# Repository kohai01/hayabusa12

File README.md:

# hayabusa12
hayabusa12 is a brother of hayabusa04 with more keys and an oled display
It allows the users to bind any macros to every key.
Now with the equipped oled display, you can customize your macropad with your favorite artwork!

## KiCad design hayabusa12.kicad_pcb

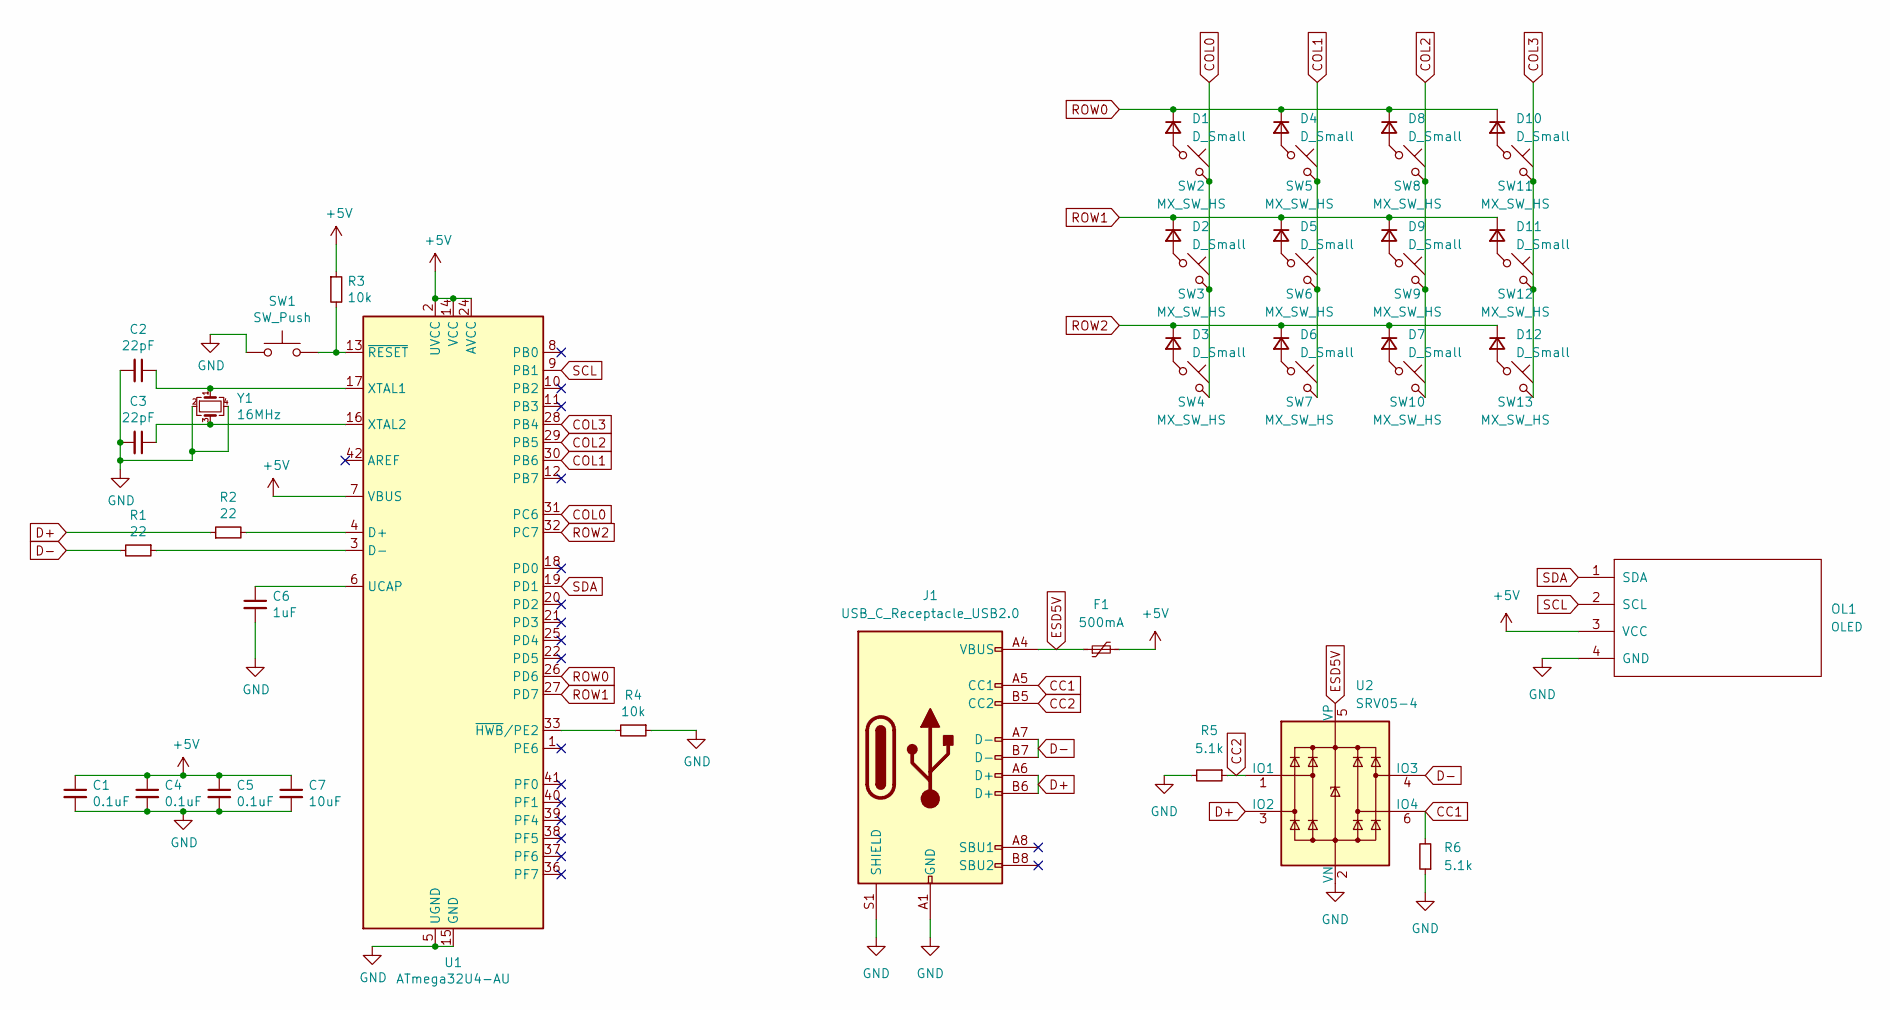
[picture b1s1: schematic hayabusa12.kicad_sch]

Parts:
C1, C4, C5: 0.1uF; C_0805_2012Metric
C2, C3: 22pF; C_0805_2012Metric
C6: 1uF; C_0805_2012Metric
C7: 10uF; C_0805_2012Metric
D1, D2, D3, D4, D5, D6, D7, D8, D9, D10, D11, D12: D_Small; D_SOD-123
F1: 500mA; Fuse_1206_3216Metric
J1: USB_C_Receptacle_USB2.0; USB_C_Receptacle_HRO_TYPE-C-31-M-12
OL1: OLED; OLED_v2
R1, R2: 22; R_0805_2012Metric
R3, R4: 10k; R_0805_2012Metric
R5, R6: 5.1k; R_0805_2012Metric
SW1: SW_Push; SW_SPST_SKQG_WithStem
SW2, SW3, SW4, SW5, SW6, SW7, SW8, SW9, SW10, SW11, SW12, SW13: MX_SW_HS; SW_MX_HS_1u
U1: ATmega32U4-AU; TQFP-44_10x10mm_P0.8mm
U2: SRV05-4; SOT-23-6
Y1: 16MHz; Crystal_SMD_3225-4Pin_3.2x2.5mm

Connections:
+5V: C1.1, C4.1, C5.1, C7.1, F1.2, OL1.3 (VCC), R3.1, U1.2 (UVCC), U1.7 (VBUS), U1.14 (VCC), U1.24 (AVCC), U1.34 (VCC), U1.44 (AVCC)
CC1: J1.A5 (CC1), R6.2, U2.6 (IO4)
CC2: J1.B5 (CC2), R5.1, U2.1 (IO1)
COL0: SW2.2, SW3.2, SW4.2, U1.31 (PC6)
COL1: SW5.2, SW6.2, SW7.2, U1.30 (PB6)
COL2: SW8.2, SW9.2, SW10.2, U1.29 (PB5)
COL3: SW11.2, SW12.2, SW13.2, U1.28 (PB4)
D+: J1.A6 (D+), J1.B6 (D+), R2.1, U2.3 (IO2)
D-: J1.A7 (D-), J1.B7 (D-), R1.2, U2.4 (IO3)
ESD5V: F1.1, J1.A4 (VBUS), J1.A9 (VBUS), J1.B4 (VBUS), J1.B9 (VBUS), U2.5 (VP)
GND: C1.2, C2.2, C3.2, C4.2, C5.2, C6.2, C7.2, J1.A1 (GND), J1.A12 (GND), J1.B1 (GND), J1.B12 (GND), J1.S1 (SHIELD), OL1.4 (GND), R4.1, R5.2, R6.1, SW1.1, U1.5 (UGND), U1.15 (GND), U1.23 (GND), U1.35 (GND), U1.43 (GND), U2.2 (VN), Y1.2, Y1.4
unnamed: C2.1, U1.17 (XTAL1), Y1.1
unnamed: C3.1, U1.16 (XTAL2), Y1.3
unnamed: C6.1, U1.6 (UCAP)
unnamed: D1.2 (A), SW2.1
unnamed: D2.2 (A), SW3.1
unnamed: D3.2 (A), SW4.1
unnamed: D4.2 (A), SW5.1
unnamed: D5.2 (A), SW6.1
unnamed: D6.2 (A), SW7.1
unnamed: D7.2 (A), SW10.1
unnamed: D8.2 (A), SW8.1
unnamed: D9.2 (A), SW9.1
unnamed: D10.2 (A), SW11.1
unnamed: D11.2 (A), SW12.1
unnamed: D12.2 (A), SW13.1
unnamed: R1.1, U1.3 (D-)
unnamed: R2.2, U1.4 (D+)
unnamed: R3.2, SW1.2, U1.13 (~RESET)
unnamed: R4.2, U1.33 (~HWB/PE2)
ROW0: D1.1 (K), D4.1 (K), D8.1 (K), D10.1 (K), U1.26 (PD6)
ROW1: D2.1 (K), D5.1 (K), D9.1 (K), D11.1 (K), U1.27 (PD7)
ROW2: D3.1 (K), D6.1 (K), D7.1 (K), D12.1 (K), U1.32 (PC7)
SCL: OL1.2 (SCL), U1.9 (PB1)
SDA: OL1.1 (SDA), U1.19 (PD1)

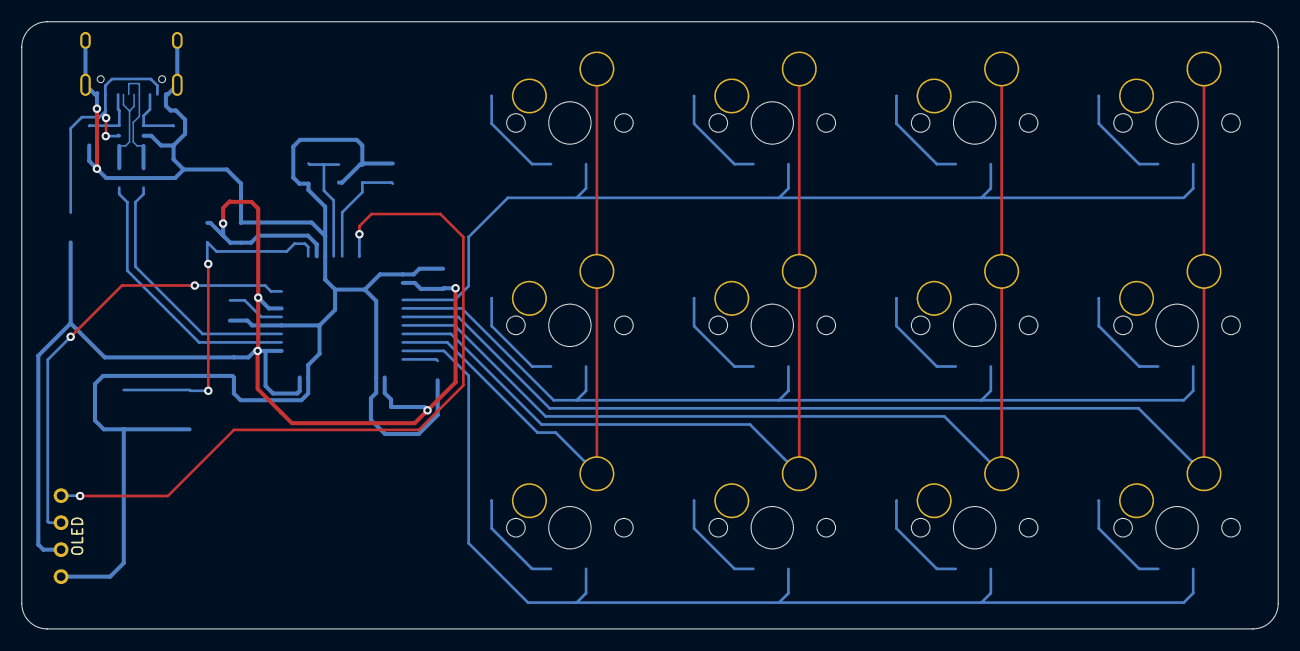
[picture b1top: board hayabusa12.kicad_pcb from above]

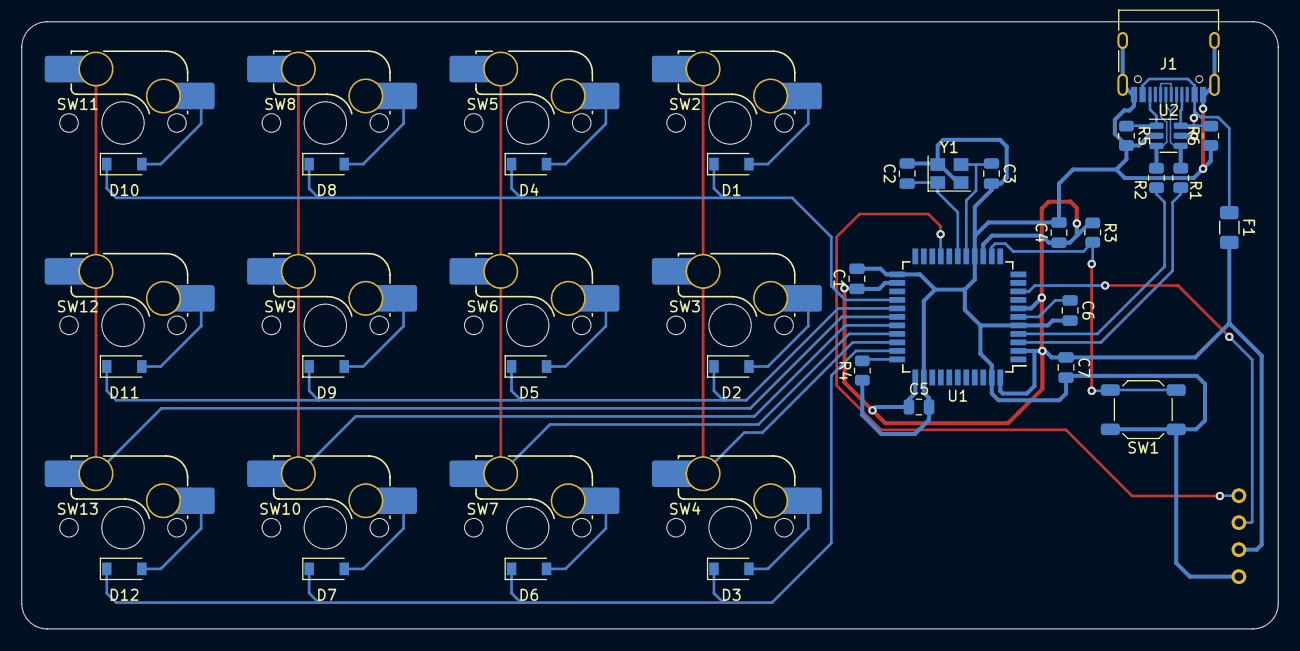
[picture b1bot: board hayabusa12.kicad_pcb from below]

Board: 2 copper layers, 118.3 x 57.1 mm, 44 parts (43 on the bottom side), 35 nets.

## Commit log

2022-12-11 completed schematics
2022-12-12 started routing
2022-12-12 updated schematics
2022-12-17 routing
2023-01-23 added diodes bc i forgor
2023-01-23 cleaned up submodules
2023-01-30 made minor changes to routing
